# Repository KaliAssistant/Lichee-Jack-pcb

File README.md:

# Lichee-Jack PCB

This repository contains the open-source extension board system for the **Lichee-Jack** project. It includes multiple PCBs, FPCs, stack-up boards, and extension modules designed to expand the capabilities of the LicheeRV Nano.

---

## Overview

The complete hardware system consists of **three main boards**:

---

### 1. `Lichee-Jack_EXT_BOARD`

The primary functional PCB containing:

* Battery management system
* WS2812 RGB LED
* SP3T control switch
* Peripheral support circuits
* PCB thickness: **1.6 mm**

---

### 2. `Lichee-Jack_EXT_BOARD_FPC`

A flexible cable connecting:

* LicheeRV Nano ETH pads → EXT board ETH pads
* LicheeRV Nano CSI pads → Header board
* Extra signals for extension modules

---

### 3. `Lichee-Jack_HEADER_BOARD`

Adapter board for:

* 1.27 mm 2×10 SMT header
* EXT_BOARD_FPC
* PCB thickness: **0.8 mm**

Used by external extension modules.

---

## Assembly Notes

> **Important:** Follow recommended solder temperatures to avoid damage.

### EXT_BOARD

* Use **high-temperature solder paste** (Sn63/Pb37 or SAC305)

### EXT_BOARD_FPC

* Solder with **standard soldering iron**

### Header Board

* Use **high-temperature solder paste**

### LicheeRV Nano + EXT Board

* Use **low-temperature solder paste** (Sn42/Bi58)

---

## Battery Information

* Recommended: **Li-Po 3.7V 200mAh**
* Model: **402030**
* Fits the 3D-printed enclosure included in the repo

---

## 5V Power Notes

The LicheeRV Nano shorts **VBUS** ↔ **VSYS** using a 0Ω resistor (marked "5V").

To safely power externally:

> **Remove the 0Ω resistor** on the bottom layer.

---

## Assembly for 3D-Printed Case Compatibility

To fit the Nano + EXT Board inside the enclosure:

### 1. Remove CSI Connector

* Desolder the CSI camera connector on the LicheeRV Nano

### 3. Install Header Board

* Solder SMT connectors based on BOM

### 4. Connect FPC

* Solder EXT_BOARD_FPC between the Header Board and the LicheeRV Nano

### 5. Ethernet Wiring

* Use short 4P or 8P RJ45 cable
* Solder wires to EXT Board ETH pads:

  * WOG, OG, WG, G → pins 1, 2, 3, 6
* Crimp 8P8C connector to cable end

---

## PCB Assembly via Manufacturer

You may order PCBA for the **EXT_BOARD** using:

* Gerber files
* BOM
* CPL

Manufacturers (JLCPCB / PCBWay / Seeed) will assemble **only the EXT_BOARD**. The LicheeRV Nano must be soldered manually unless custom services are arranged.

---

## PCB Version History

Always use the latest revision.

### v1.0 → v1.1

* Added missing Schottky diode between PWR_IN → PWR_OUT
* Fixed boot issue by rerouting SP3T pos1 from GPIO-A16 → GPIO-A15
* See diagram:

### v1.1 → v1.0.32 (EXT_BOARD)

* Fixed UART0-RX conflict (GPIO-A17)
* Rerouted pos2 → GPIO-A24
* Added speaker pads
* Replaced old ETH-FPC system with:

  * Stack board
  * Header board
  * New EXT_BOARD_FPC

---

## License

Licensed under **GNU GPLv3**.

You are free to **use**, **modify**, **study**, and **redistribute** this project under the same license.

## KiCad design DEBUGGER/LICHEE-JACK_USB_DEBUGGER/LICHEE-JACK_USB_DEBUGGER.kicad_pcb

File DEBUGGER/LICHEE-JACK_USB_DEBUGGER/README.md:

# Lichee-Jack USB Debugger

This sub-directory contains the **USB 2.0 hub + UART converter board** designed specifically for the **Lichee-Jack** project.
It is intended to simplify development, debugging, and flashing by combining **USB OTG**, **UART console**, and **power control** into a single compact board.

---

## Overview

The **LicheeRV Nano** features a **USB 2.0 Type-C OTG port implemented directly by the SoC PHY**.
This design is slightly different from a typical USB 2.0 Type-C implementation:

* **SUB1 / SUB2** pins are internally multiplexed as **SoC UART0**

  * Used for early boot logs, kernel `printk`, and Linux login console
* **D+ / D-** pins are used as a standard **USB OTG interface**

  * Used for USB gadget mode (RNDIS, ECM, HID, Mass Storage, etc.)

Because UART and USB share the same physical Type-C connector, direct connection to a PC is inconvenient during development.

> [!IMPORTANT]
> This board is **not a generic USB-C hub**.
>
> It is designed specifically around the **LicheeRV Nano Type-C PHY behavior**,
> where **USB OTG and UART share the same connector**.
> Using it with unrelated USB-C devices may lead to undefined behavior.

To solve this, the **Lichee-Jack USB Debugger** acts as a **2-port Type-C converter**:

* **Port 1 (Upstream)** → Connects to the host PC
* **Port 2 (Downstream)** → Connects to the Lichee-Jack device

The board cleanly separates:

* USB OTG data path
* UART debug console
* Power and connection detection

---

## Architecture & Design

### USB Hub

The board uses a **Microchip USB2422/MJ** USB 2.0 hub controller:

* **1 upstream port** (PC)
* **2 downstream ports**

  * One for Lichee-Jack USB OTG
  * One internally connected to the USB-UART bridge

This allows the Lichee-Jack USB gadget functions to work normally **while UART is simultaneously available** on the same PC connection.

> [!NOTE]
> The hub architecture allows **USB gadget functions and UART console**
> to operate **simultaneously over a single PC connection**.
> No cable swapping or re-plugging is required during development.

### USB-UART Bridge

UART is provided by **CP2102-GMR**:

* Connected to Lichee-Jack **UART0 (SUB1 / SUB2)**
* Exposes a standard USB CDC-ACM serial device on the host
* Suitable for:

  * U-Boot console
  * Linux kernel logs
  * Root login shell

### Type-C CC & Power Control

The debugger board implements **CC-based power detection and control**:

* **PMOS power switch** controlled by CC logic
* Behavior:

  * If **Lichee-Jack is not connected**, PMOS remains **OFF**
  * When Lichee-Jack is connected:

    * CC pins are pulled down by the device
    * PMOS gate is driven
    * Power path is enabled automatically

This prevents:

* Back-powering
* Floating VBUS issues
* Accidental short or unstable power states

> [!NOTE]
> Power delivery on this board is **fully hardware-controlled via CC detection**.
> No firmware or software control is involved.

---

## Features

* USB 2.0 Hub (1-up / 2-down)
* Integrated USB-UART console
* Native support for LicheeRV Nano Type-C pin multiplexing
* Automatic CC-based power switching
* Works seamlessly with USB gadget modes
* No firmware required (fully hardware-driven)

---

## Assembly

* **PCB**: 2-layer board, thickness 1.6 mm
* **Assembly side**: Top side only
* **Solder paste**:

  * Sn63 / Pb37 **or**
  * SAC305

> [!CAUTION]
> The USB hub uses a **QFN package** and requires a **proper reflow profile**.
>
> Insufficient temperature or uneven heating may cause:
>
> * Hidden cold joints
> * Unreliable USB enumeration
>
> A controlled **high-temperature reflow process** is strongly recommended.

---

## PCBA

* All components placed on **top layer only**
* Suitable for low-cost SMT assembly

The following files are provided in the **EXT-Board** latest release:

* BOM (Bill of Materials)
* CPL / Pick-and-Place
* Gerber files

---

## Notes

> [!WARNING]
> **Type-C cable selection is critical.**
>
> Many USB 3.x Type-C cables are **SuperSpeed-only** and **do not carry USB-2 / SBU signals**.
> If such a cable is used, **SUB1 / SUB2 (UART0)** may be physically disconnected,
> resulting in **no UART console output** even when the hardware is correct.
>
> Always use a **Thunderbolt / USB4 Type-C cable**, which is required by specification
> to include **full USB-2 wiring**.

> [!TIP]
> **No UART console? Try flipping the Type-C connector on the Lichee-Jack side.**
>
> Unlike USB D+ / D-, **SUB1 / SUB2 (UART0) are not orientation-symmetric**.
> Depending on plug orientation, the UART pins may not be connected.
>
> Simply unplug and **reverse the Type-C connector** to restore UART functionality.

* Designed specifically for **Lichee-Jack / LicheeRV Nano** Type-C behavior
* Not intended as a generic USB-C hub
* Recommended for development, debugging, and factory flashing workflows

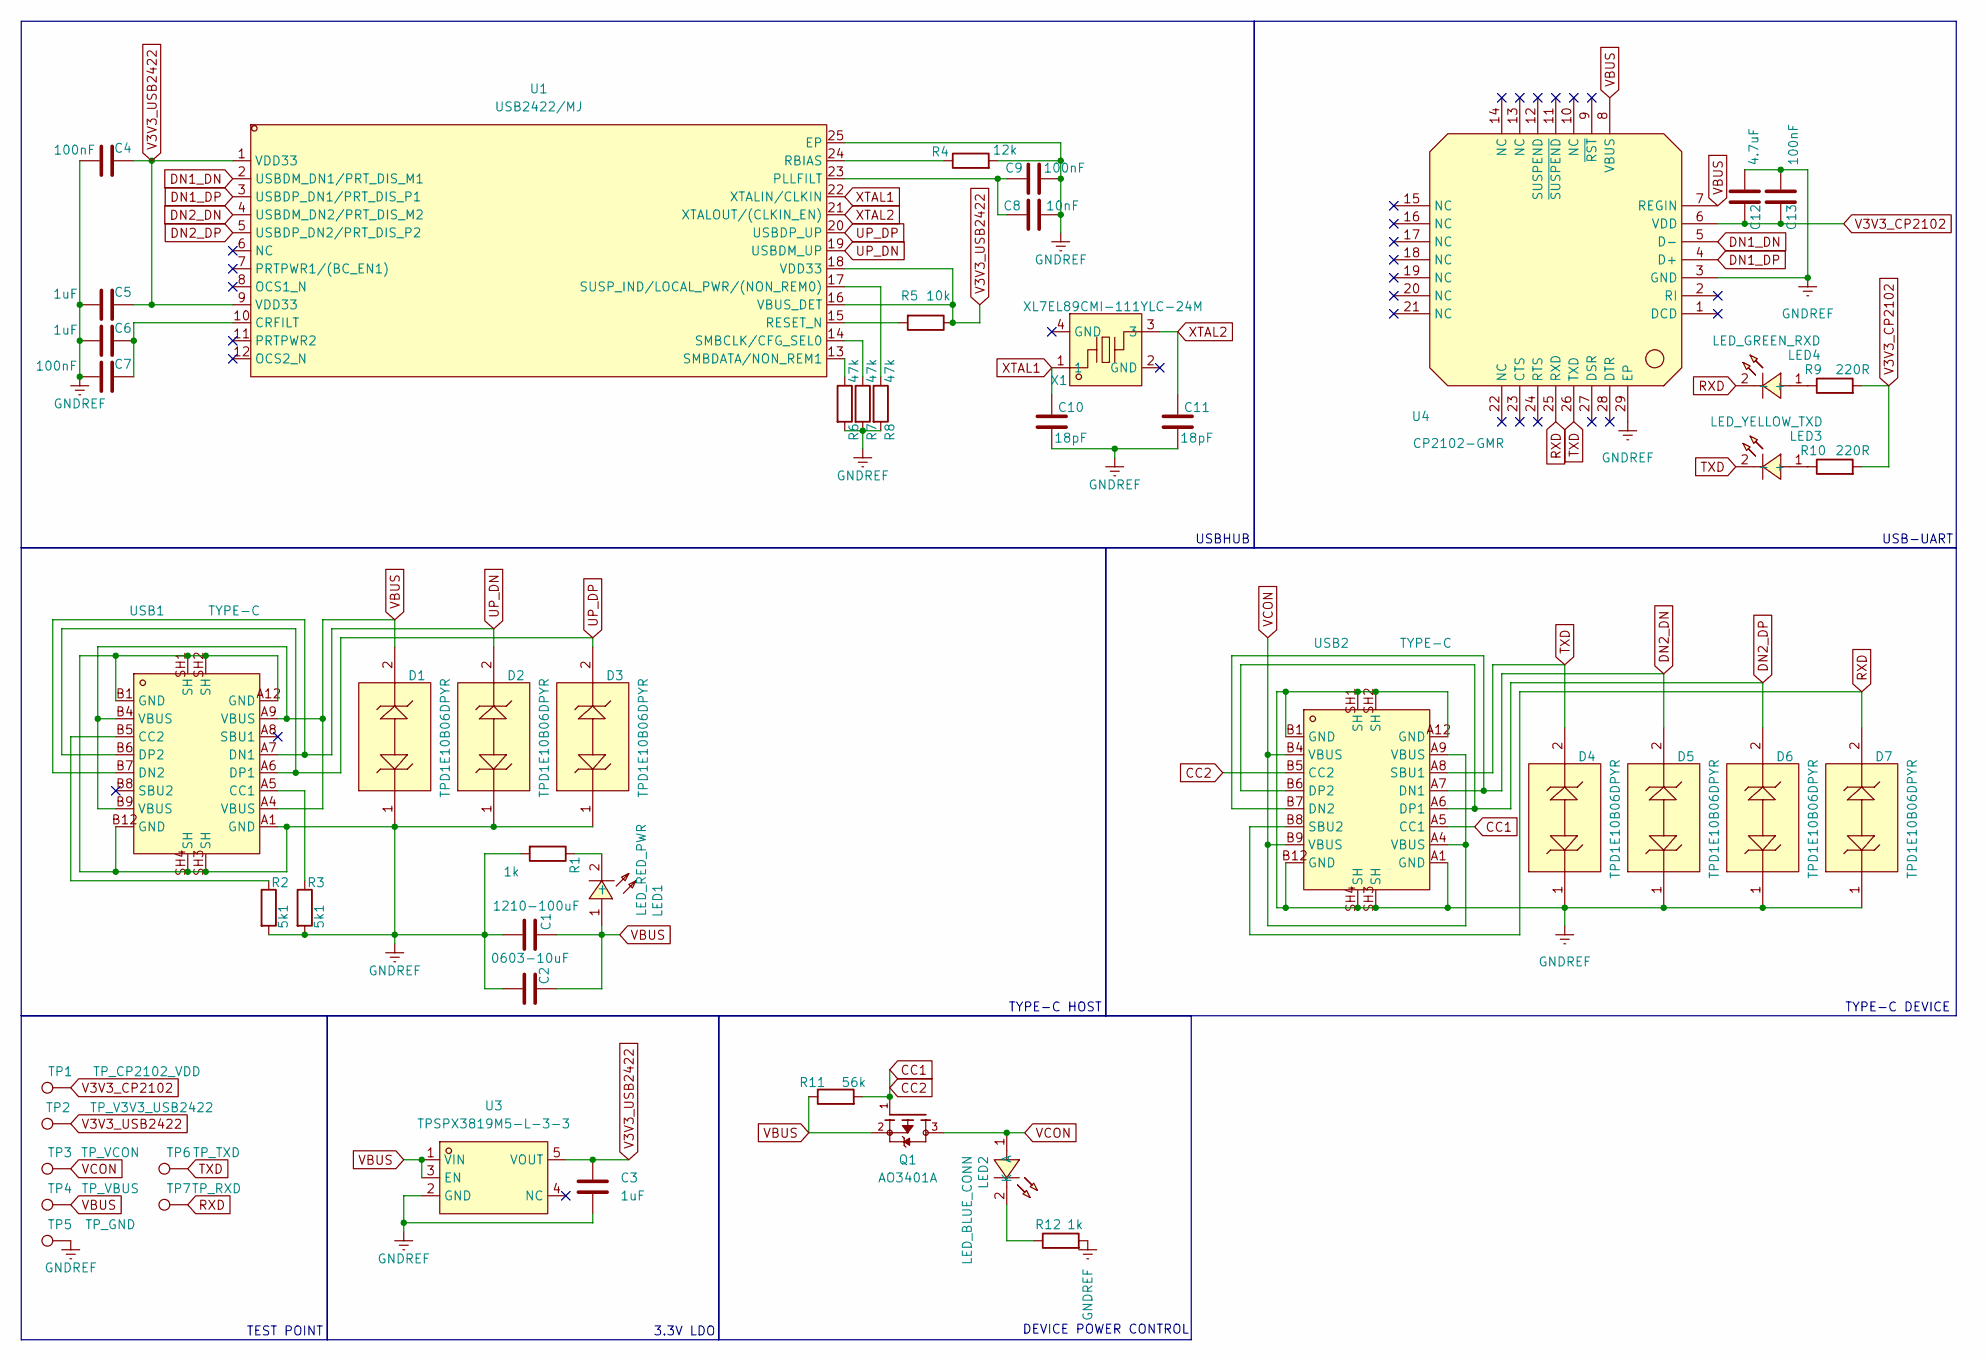
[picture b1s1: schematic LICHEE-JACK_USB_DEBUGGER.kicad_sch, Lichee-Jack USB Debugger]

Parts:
C1: 1210-100uF; C_1210_3225Metric
C2: 0603-10uF; C_0603_1608Metric
C3, C5, C6: 1uF; C_0402_1005Metric
C4, C7, C9, C13: 100nF; C_0402_1005Metric
C8: 10nF; C_0402_1005Metric
C10, C11: 18pF; C_0402_1005Metric
C12: 4.7uF; C_0402_1005Metric
D1, D2, D3, D4, D5, D6, D7: TPD1E10B06DPYR; X1SON-2_L1.0-W0.6-P0.65-BI; LCSC Part C48260
LED1: LED_RED_PWR; LED0603-FD; LCSC Part C19171390
LED2: LED_BLUE_CONN; LED0603-FD; LCSC Part C19171394
LED3: LED_YELLOW_TXD; LED0603-FD; LCSC Part C19273151
LED4: LED_GREEN_RXD; LED0603-FD; LCSC Part C19273151
Q1: AO3401A; SOT23-3
R1, R12: 1k; R_0402_1005Metric
R2, R3: 5k1; R_0402_1005Metric
R4: 12k; R_0402_1005Metric
R5: 10k; R_0402_1005Metric
R6, R7, R8: 47k; R_0402_1005Metric
R9, R10: 220R; R_0402_1005Metric
R11: 56k; R_0402_1005Metric
TP1: TP_CP2102_VDD; TestPoint_Pad_D1.0mm
TP2: TP_V3V3_USB2422; TestPoint_Pad_D1.0mm
TP3: TP_VCON; TestPoint_Pad_D1.0mm
TP4: TP_VBUS; TestPoint_Pad_D1.0mm
TP5: TP_GND; TestPoint_Pad_D1.0mm
TP6: TP_TXD; TestPoint_Pad_D1.0mm
TP7: TP_RXD; TestPoint_Pad_D1.0mm
U1: USB2422/MJ; QFN-24_L4.0-W4.0-P0.50-BL-EP2.6; LCSC Part C633330
U3: TPSPX3819M5-L-3-3; SOT-23-5_L3.0-W1.6-P0.95-LS2.8-BR; LCSC Part C5370980
U4: CP2102-GMR; WQFN-28_L5.0-W5.0-P0.50-BL-EP3.2; LCSC Part C6568
USB1, USB2: TYPE-C; USB-C_SMD-TYPE-C-31-M-12; LCSC Part C2927038
X1: XL7EL89CMI-111YLC-24M; CRYSTAL-SMD_4P-L2.0-W1.6-BL; LCSC Part C2965581

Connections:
CC1: Q1.1, R11.2, USB2.A5 (CC1), USB2.B5 (CC2)
DN1_DN: U1.2 (USBDM_DN1/PRT_DIS_M1), U4.5 (D-)
DN1_DP: U1.3 (USBDP_DN1/PRT_DIS_P1), U4.4 (D+)
DN2_DN: D5.2, U1.4 (USBDM_DN2/PRT_DIS_M2), USB2.A7 (DN1), USB2.B7 (DN2)
DN2_DP: D6.2, U1.5 (USBDP_DN2/PRT_DIS_P2), USB2.A6 (DP1), USB2.B6 (DP2)
GNDREF: C1.2, C2.2, C3.2, C4.2, C5.2, C6.2, C7.2, C8.1, C9.1, C10.2, C11.2, C12.1, C13.1, D1.1, D2.1, D3.1, D4.1, D5.1, D6.1, D7.1, R1.2, R2.2, R3.2, R4.2, R6.2, R7.2, R8.2, R12.2, TP5.1, U1.25 (EP), U3.2 (GND), U4.3 (GND), U4.29 (EP), USB1.A1 (GND), USB1.A12 (GND), USB1.B1 (GND), USB1.B12 (GND), USB1.SH1 (SH), USB1.SH2 (SH), USB1.SH3 (SH), USB1.SH4 (SH), USB2.A1 (GND), USB2.A12 (GND), USB2.B1 (GND), USB2.B12 (GND), USB2.SH1 (SH), USB2.SH2 (SH), USB2.SH3 (SH), USB2.SH4 (SH)
unnamed: LED1.2 (-), R1.1
unnamed: LED2.2 (K), R12.1
unnamed: LED3.1 (+), R10.1
unnamed: LED4.1 (+), R9.1
unnamed: C6.1, C7.1, U1.10 (CRFILT)
unnamed: C8.2, C9.2, U1.23 (PLLFILT)
unnamed: R4.1, U1.24 (RBIAS)
unnamed: R5.2, U1.15 (RESET_N)
unnamed: R7.1, U1.14 (SMBCLK/CFG_SEL0)
unnamed: R6.1, U1.13 (SMBDATA/NON_REM1)
unnamed: R8.1, U1.17 (SUSP_IND/LOCAL_PWR/(NON_REM0))
unnamed: R3.1, USB1.A5 (CC1)
unnamed: R2.1, USB1.B5 (CC2)
RXD: D7.2, LED4.2 (-), TP7.1, U4.25 (RXD), USB2.B8 (SBU2)
TXD: D4.2, LED3.2 (-), TP6.1, U4.26 (TXD), USB2.A8 (SBU1)
UP_DN: D2.2, U1.19 (USBDM_UP), USB1.A7 (DN1), USB1.B7 (DN2)
UP_DP: D3.2, U1.20 (USBDP_UP), USB1.A6 (DP1), USB1.B6 (DP2)
V3V3_CP2102: C12.2, C13.2, R9.2, R10.2, TP1.1, U4.6 (VDD)
V3V3_USB2422: C3.1, C4.1, C5.1, R5.1, TP2.1, U1.1 (VDD33), U1.9 (VDD33), U1.16 (VBUS_DET), U1.18 (VDD33), U3.5 (VOUT)
VBUS: C1.1, C2.1, D1.2, LED1.1 (+), Q1.2, R11.1, TP4.1, U3.1 (VIN), U3.3 (EN), U4.7 (REGIN), U4.8 (VBUS), USB1.A4 (VBUS), USB1.A9 (VBUS), USB1.B4 (VBUS), USB1.B9 (VBUS)
VCON: LED2.1 (A), Q1.3, TP3.1, USB2.A4 (VBUS), USB2.A9 (VBUS), USB2.B4 (VBUS), USB2.B9 (VBUS)
XTAL1: C10.1, U1.22 (XTALIN/CLKIN), X1.1
XTAL2: C11.1, U1.21 (XTALOUT/(CLKIN_EN)), X1.3

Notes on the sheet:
TYPE-C HOST
USB-UART
DEVICE POWER CONTROL
3.3V LDO
USBHUB
TYPE-C DEVICE
TEST POINT

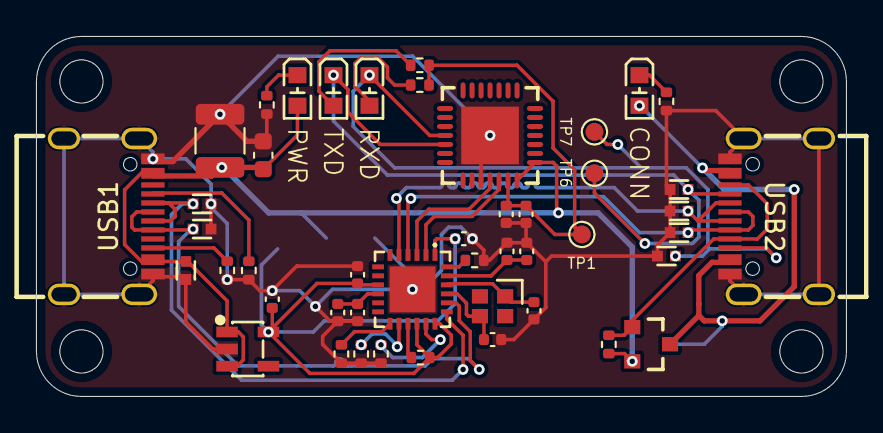
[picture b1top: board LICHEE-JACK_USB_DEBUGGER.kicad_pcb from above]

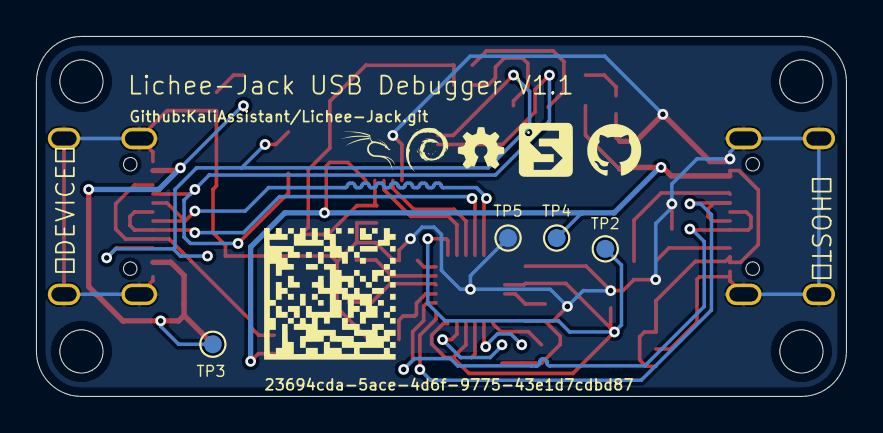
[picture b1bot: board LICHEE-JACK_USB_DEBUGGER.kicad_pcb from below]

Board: 2 copper layers, 45.0 x 20.0 mm, 50 parts (4 on the bottom side), 29 nets.

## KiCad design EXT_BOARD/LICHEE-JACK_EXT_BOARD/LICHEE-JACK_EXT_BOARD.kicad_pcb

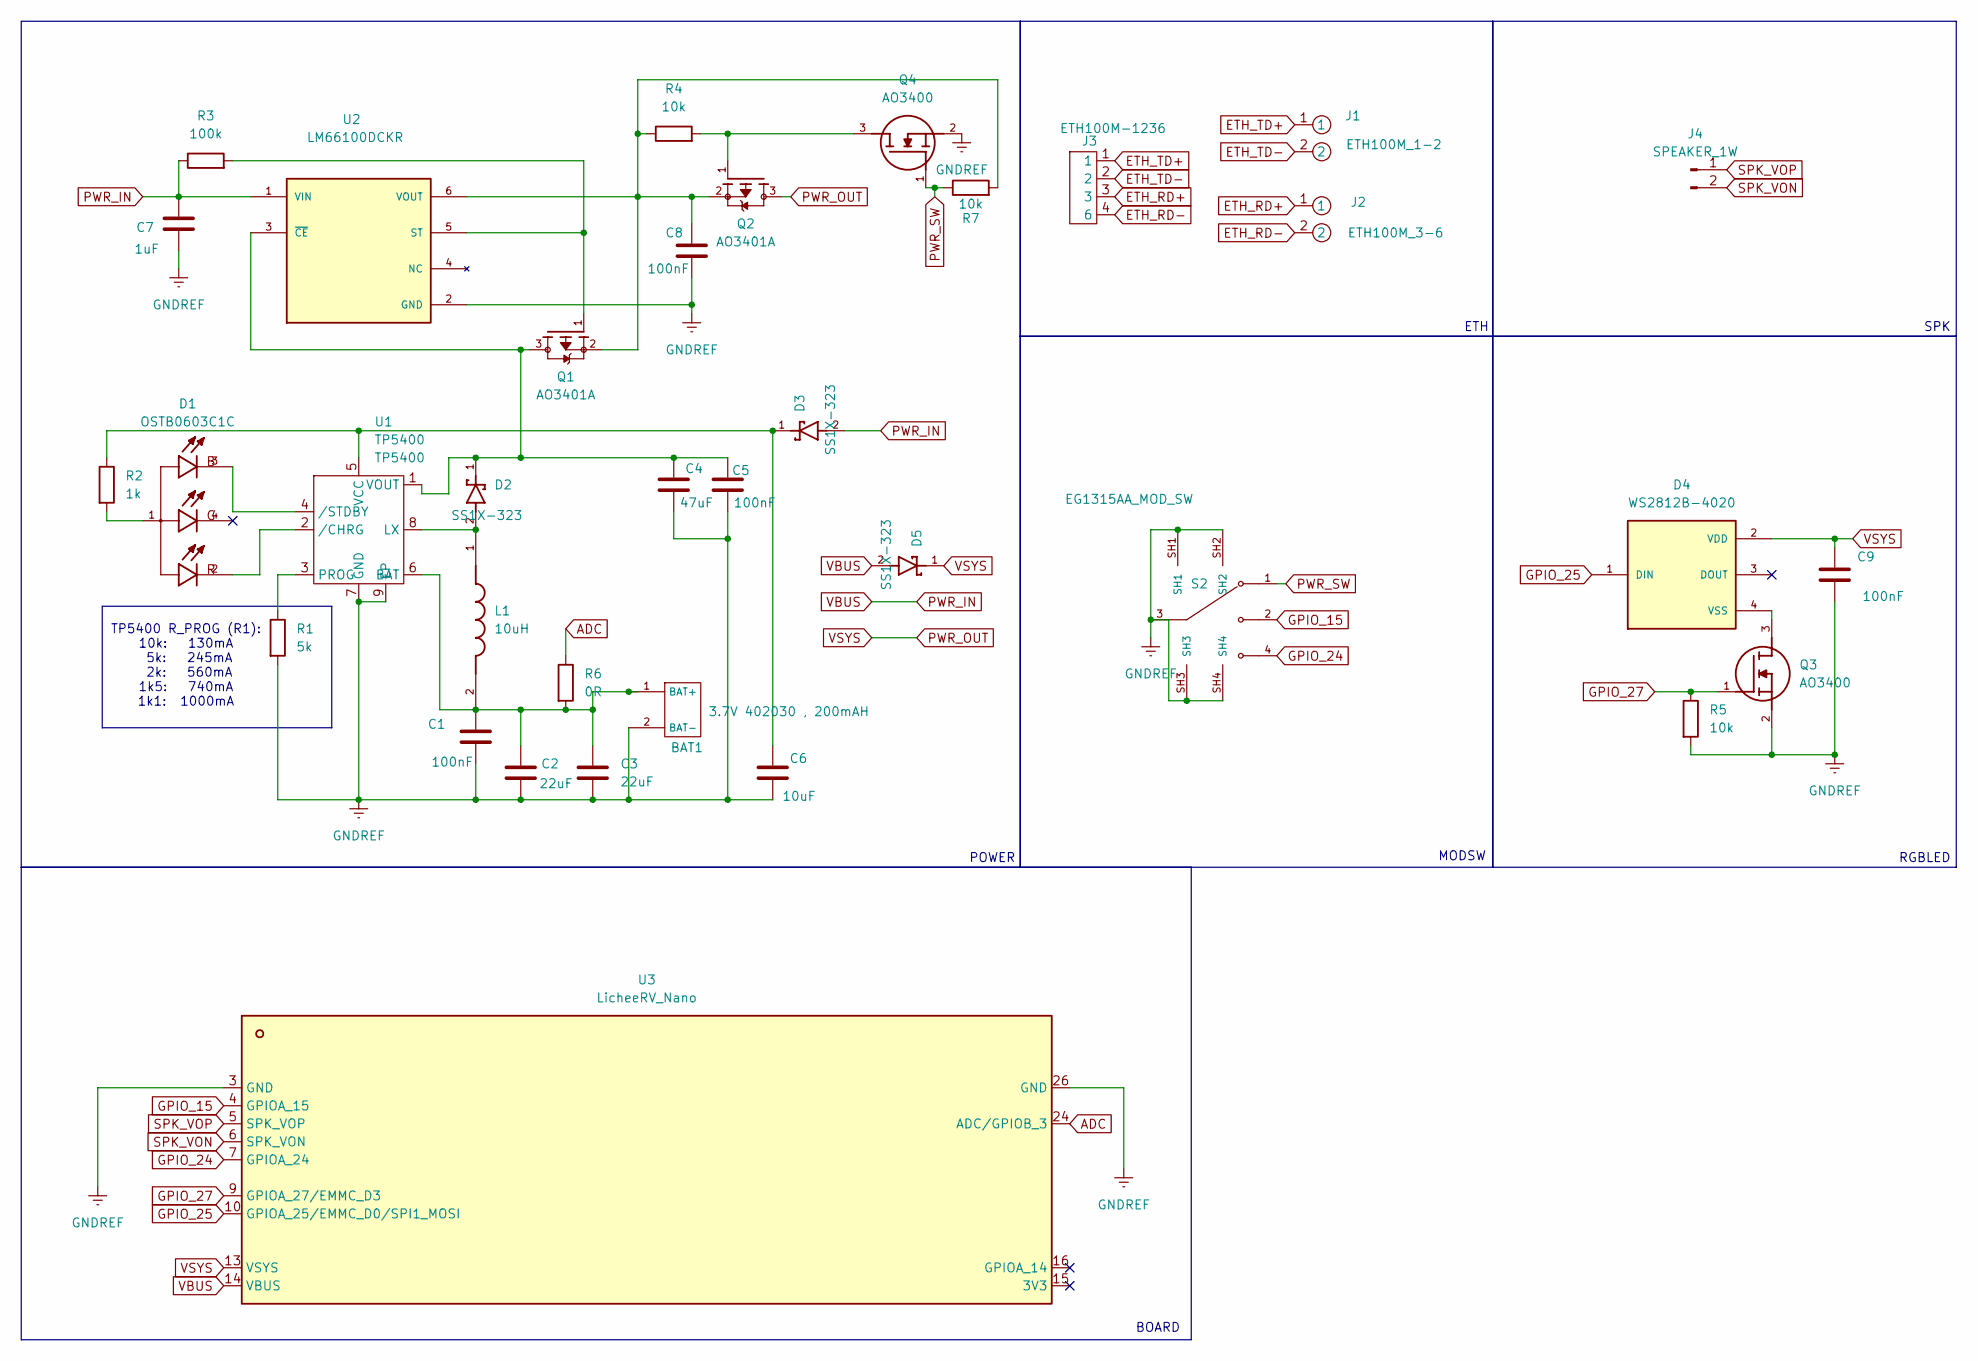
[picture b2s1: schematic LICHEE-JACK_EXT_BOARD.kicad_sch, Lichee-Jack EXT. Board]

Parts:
BAT1: 3.7V 402030 , 200mAH; BAT_PAD
C1, C5, C8, C9: 100nF; C_0402_1005Metric
C2, C3: 22uF; C_0805_2012Metric
C4: 47uF; C_0805_2012Metric
C6: 10uF; C_0603_1608Metric
C7: 1uF; C_0402_1005Metric
D1: OSTB0603C1C; LED_OSTB0603C1C; PARTREV A.3
D2, D3, D5: SS1X-323; DIO_PMEG4010CEJ_115; PARTREV 02
D4: WS2812B-4020; LED_WS2812B-4020; PARTREV V1.2
J1: ETH100M_1-2; ETHPAD
J2: ETH100M_3-6; ETHPAD
J3: ETH100M-1236; ETHCON
J4: SPEAKER_1W; SPK_PAD
L1: 10uH; ASPI-4030S-XXXM-T; PARTREV 03.09.13
Q1, Q2: AO3401A; SOT23-3
Q3, Q4: AO3400; SOT95P280X125-3N; MANUFACTURER_PART_NUMBER AO3400
R1: 5k; R_0402_1005Metric
R2: 1k; R_0603_1608Metric
R3: 100k; R_0402_1005Metric
R4, R5, R7: 10k; R_0402_1005Metric
R6: 0R; R_0402_1005Metric
S2: EG1315AA_MOD_SW; SW_EG1315AA; PARTREV 7.13.2018
U1: TP5400; SOIC-8-1EP_3.9x4.9mm_P1.27mm_EP2.29x3mm
U2: LM66100DCKR; SOT65P210X110-6N; PARTREV Rev. A
U3: LicheeRV_Nano; LicheeRV_Nano_MD

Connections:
ADC: R6.1, U3.24 (ADC/GPIOB_3)
ETH_RD+: J2.1, J3.3
ETH_RD-: J2.2, J3.4 (6)
ETH_TD+: J1.1, J3.1
ETH_TD-: J1.2, J3.2
GNDREF: BAT1.2 (BAT-), C1.2, C2.2, C3.2, C4.2, C5.2, C6.2, C7.2, C8.2, C9.2, Q3.2, Q4.2, R1.2, R5.2, S2.3, S2.SH1, S2.SH2, S2.SH3, S2.SH4, U1.7 (GND), U1.9 (EP), U2.2 (GND), U3.3 (GND), U3.26 (GND)
GPIO_15: S2.2, U3.4 (GPIOA_15)
GPIO_24: S2.4, U3.7 (GPIOA_24)
GPIO_25: D4.1 (DIN), U3.10 (GPIOA_25/EMMC_D0/SPI1_MOSI)
GPIO_27: Q3.1, R5.1, U3.9 (GPIOA_27/EMMC_D3)
unnamed: BAT1.1 (BAT+), C1.1, C2.1, C3.1, L1.2, R6.2, U1.6 (BAT)
unnamed: D1.1, R2.2
unnamed: D4.4 (VSS), Q3.3
unnamed: Q2.1, Q4.3, R4.2
unnamed: D2.2, L1.1, U1.8 (LX)
unnamed: R1.1, U1.3 (PROG)
unnamed: C6.1, D3.1, R2.1, U1.5 (VCC)
unnamed: C4.1, C5.1, D2.1, Q1.3, U1.1 (VOUT), U2.3 (~CE)
unnamed: D1.2, U1.2 (/CHRG)
unnamed: D1.3, U1.4 (/STDBY)
unnamed: Q1.1, R3.2, U2.5 (ST)
unnamed: C8.1, Q1.2, Q2.2, R4.1, R7.2, U2.6 (VOUT)
PWR_IN: C7.1, D3.2, D5.2, R3.1, U2.1 (VIN), U3.14 (VBUS)
PWR_OUT: C9.1, D4.2 (VDD), D5.1, Q2.3, U3.13 (VSYS)
PWR_SW: Q4.1, R7.1, S2.1
SPK_VON: J4.2, U3.6 (SPK_VON)
SPK_VOP: J4.1, U3.5 (SPK_VOP)

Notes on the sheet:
ETH
BOARD
RGBLED
MODSW
SPK
TP5400 R_PROG (R1): 10k: 130mA 5k: 245mA 2k: 560mA 1k5: 740mA 1k1: 1000mA
POWER

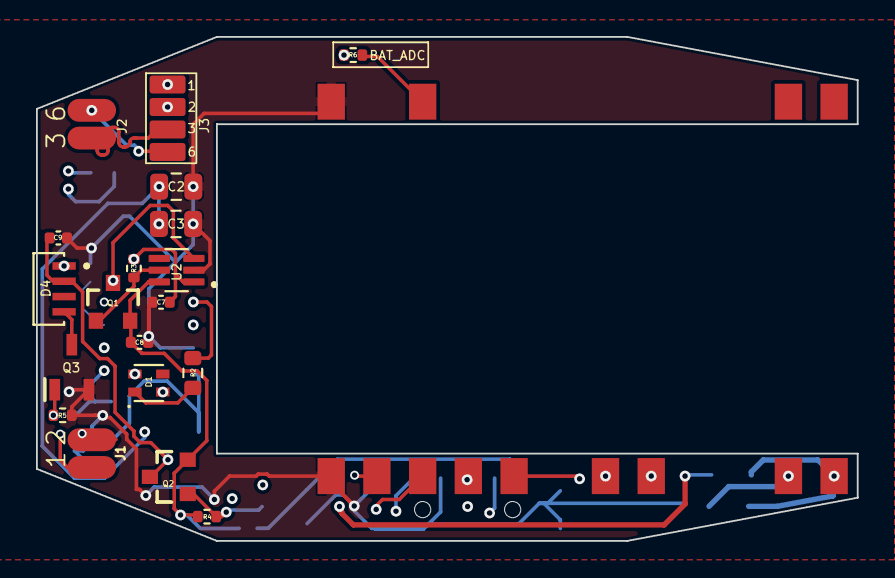
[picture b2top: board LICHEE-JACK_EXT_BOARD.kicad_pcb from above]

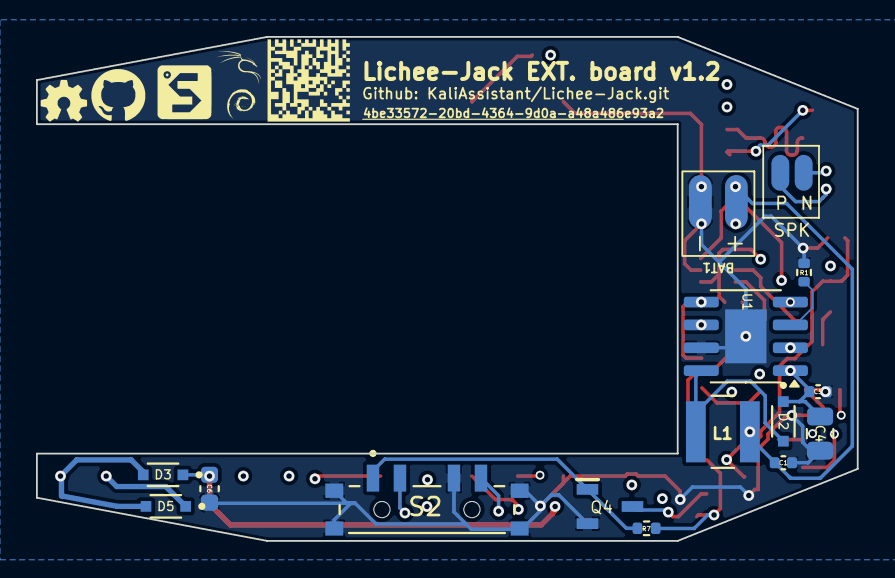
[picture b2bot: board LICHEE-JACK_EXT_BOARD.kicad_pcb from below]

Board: 4 copper layers, 45.6 x 28.0 mm, 35 parts (15 on the bottom side), 27 nets.

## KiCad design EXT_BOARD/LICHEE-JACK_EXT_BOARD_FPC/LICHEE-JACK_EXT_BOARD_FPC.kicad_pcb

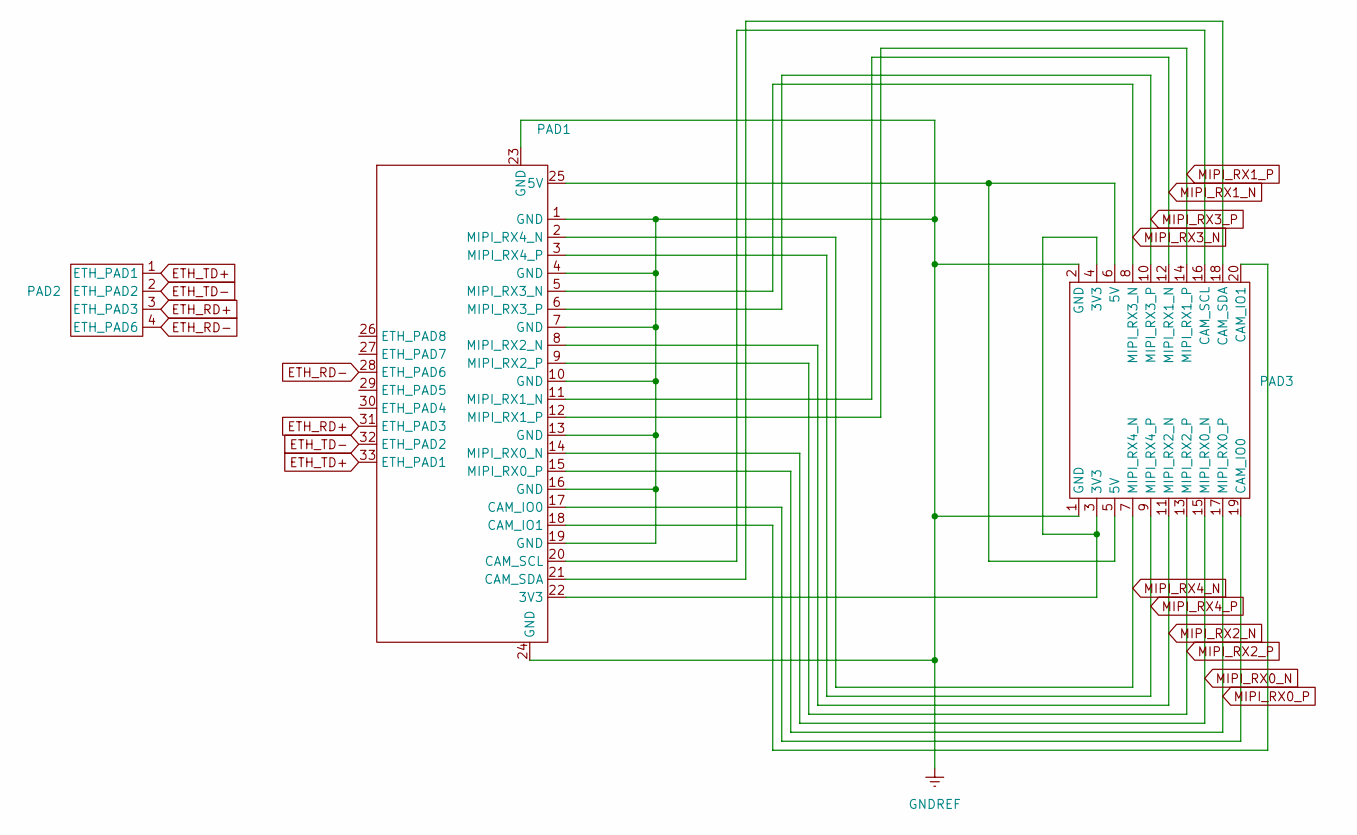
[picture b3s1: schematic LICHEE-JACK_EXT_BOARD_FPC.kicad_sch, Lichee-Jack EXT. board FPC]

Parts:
PAD1: _TO_STACK_BOARD_
PAD2: ETH_PAD
PAD3: HEADER_PAD

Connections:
ETH_RD+: PAD1.31 (ETH_PAD3), PAD2.3 (ETH_PAD3)
ETH_RD-: PAD1.28 (ETH_PAD6), PAD2.4 (ETH_PAD6)
ETH_TD+: PAD1.33 (ETH_PAD1), PAD2.1 (ETH_PAD1)
ETH_TD-: PAD1.32 (ETH_PAD2), PAD2.2 (ETH_PAD2)
GNDREF: PAD1.1 (GND), PAD1.4 (GND), PAD1.7 (GND), PAD1.10 (GND), PAD1.13 (GND), PAD1.16 (GND), PAD1.19 (GND), PAD1.23 (GND), PAD1.24 (GND), PAD3.1 (GND), PAD3.2 (GND)
MIPI_RX0_N: PAD1.14 (MIPI_RX0_N), PAD3.15 (MIPI_RX0_N)
MIPI_RX0_P: PAD1.15 (MIPI_RX0_P), PAD3.17 (MIPI_RX0_P)
MIPI_RX1_N: PAD1.11 (MIPI_RX1_N), PAD3.12 (MIPI_RX1_N)
MIPI_RX1_P: PAD1.12 (MIPI_RX1_P), PAD3.14 (MIPI_RX1_P)
MIPI_RX2_N: PAD1.8 (MIPI_RX2_N), PAD3.11 (MIPI_RX2_N)
MIPI_RX2_P: PAD1.9 (MIPI_RX2_P), PAD3.13 (MIPI_RX2_P)
MIPI_RX3_N: PAD1.5 (MIPI_RX3_N), PAD3.8 (MIPI_RX3_N)
MIPI_RX3_P: PAD1.6 (MIPI_RX3_P), PAD3.10 (MIPI_RX3_P)
MIPI_RX4_N: PAD1.2 (MIPI_RX4_N), PAD3.7 (MIPI_RX4_N)
MIPI_RX4_P: PAD1.3 (MIPI_RX4_P), PAD3.9 (MIPI_RX4_P)
unnamed: PAD1.22 (3V3), PAD3.3 (3V3), PAD3.4 (3V3)
unnamed: PAD1.25 (5V), PAD3.5 (5V), PAD3.6 (5V)
unnamed: PAD1.17 (CAM_IO0), PAD3.19 (CAM_IO0)
unnamed: PAD1.18 (CAM_IO1), PAD3.20 (CAM_IO1)
unnamed: PAD1.20 (CAM_SCL), PAD3.16 (CAM_SCL)
unnamed: PAD1.21 (CAM_SDA), PAD3.18 (CAM_SDA)

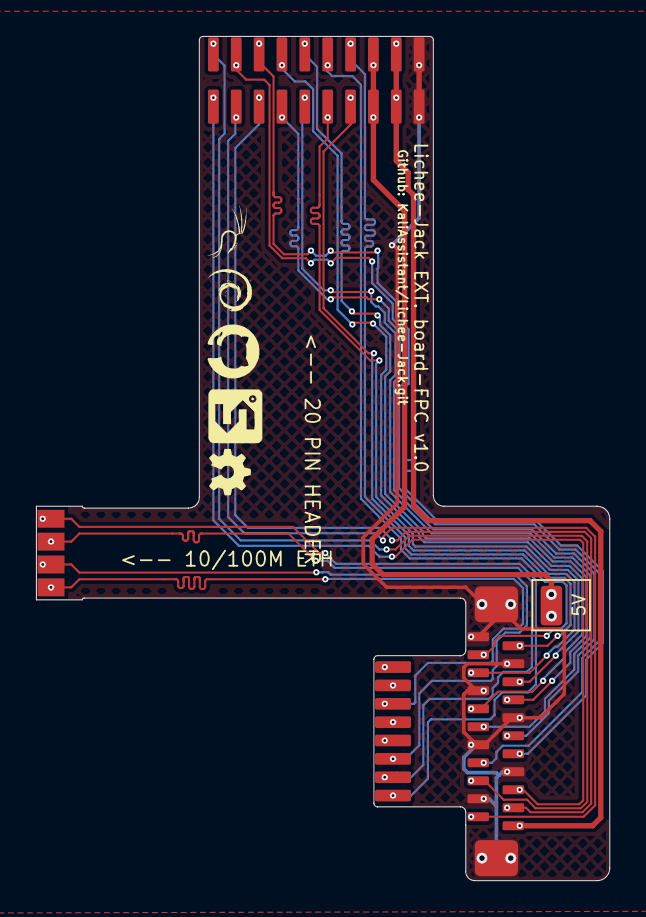
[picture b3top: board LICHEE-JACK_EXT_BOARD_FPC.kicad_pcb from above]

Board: 2 copper layers, 31.9 x 46.9 mm, 3 parts (0 on the bottom side), 21 nets.

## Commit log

2025-09-16 v1.0
2025-09-16 v1.1
2025-09-17 GPIOA16 -> GPIOA15, PWRIN-PWRVBUS ADD DIODE
2025-09-29 README
2025-09-29 GPL3
2025-12-26 v1.0.32
2025-12-27 update some files
2026-01-11 New PCB Design: Lichee-Jack USB Debugger
2026-01-12 replace some obj
2026-01-13 update some info
2026-01-13 rename LED5
2026-01-14 rename LED3
2026-01-14 case problem, delete dup
2026-01-14 add USB Debugger README
2026-01-17 fix TX/RX LED, USB DEBUGGER v1.1
